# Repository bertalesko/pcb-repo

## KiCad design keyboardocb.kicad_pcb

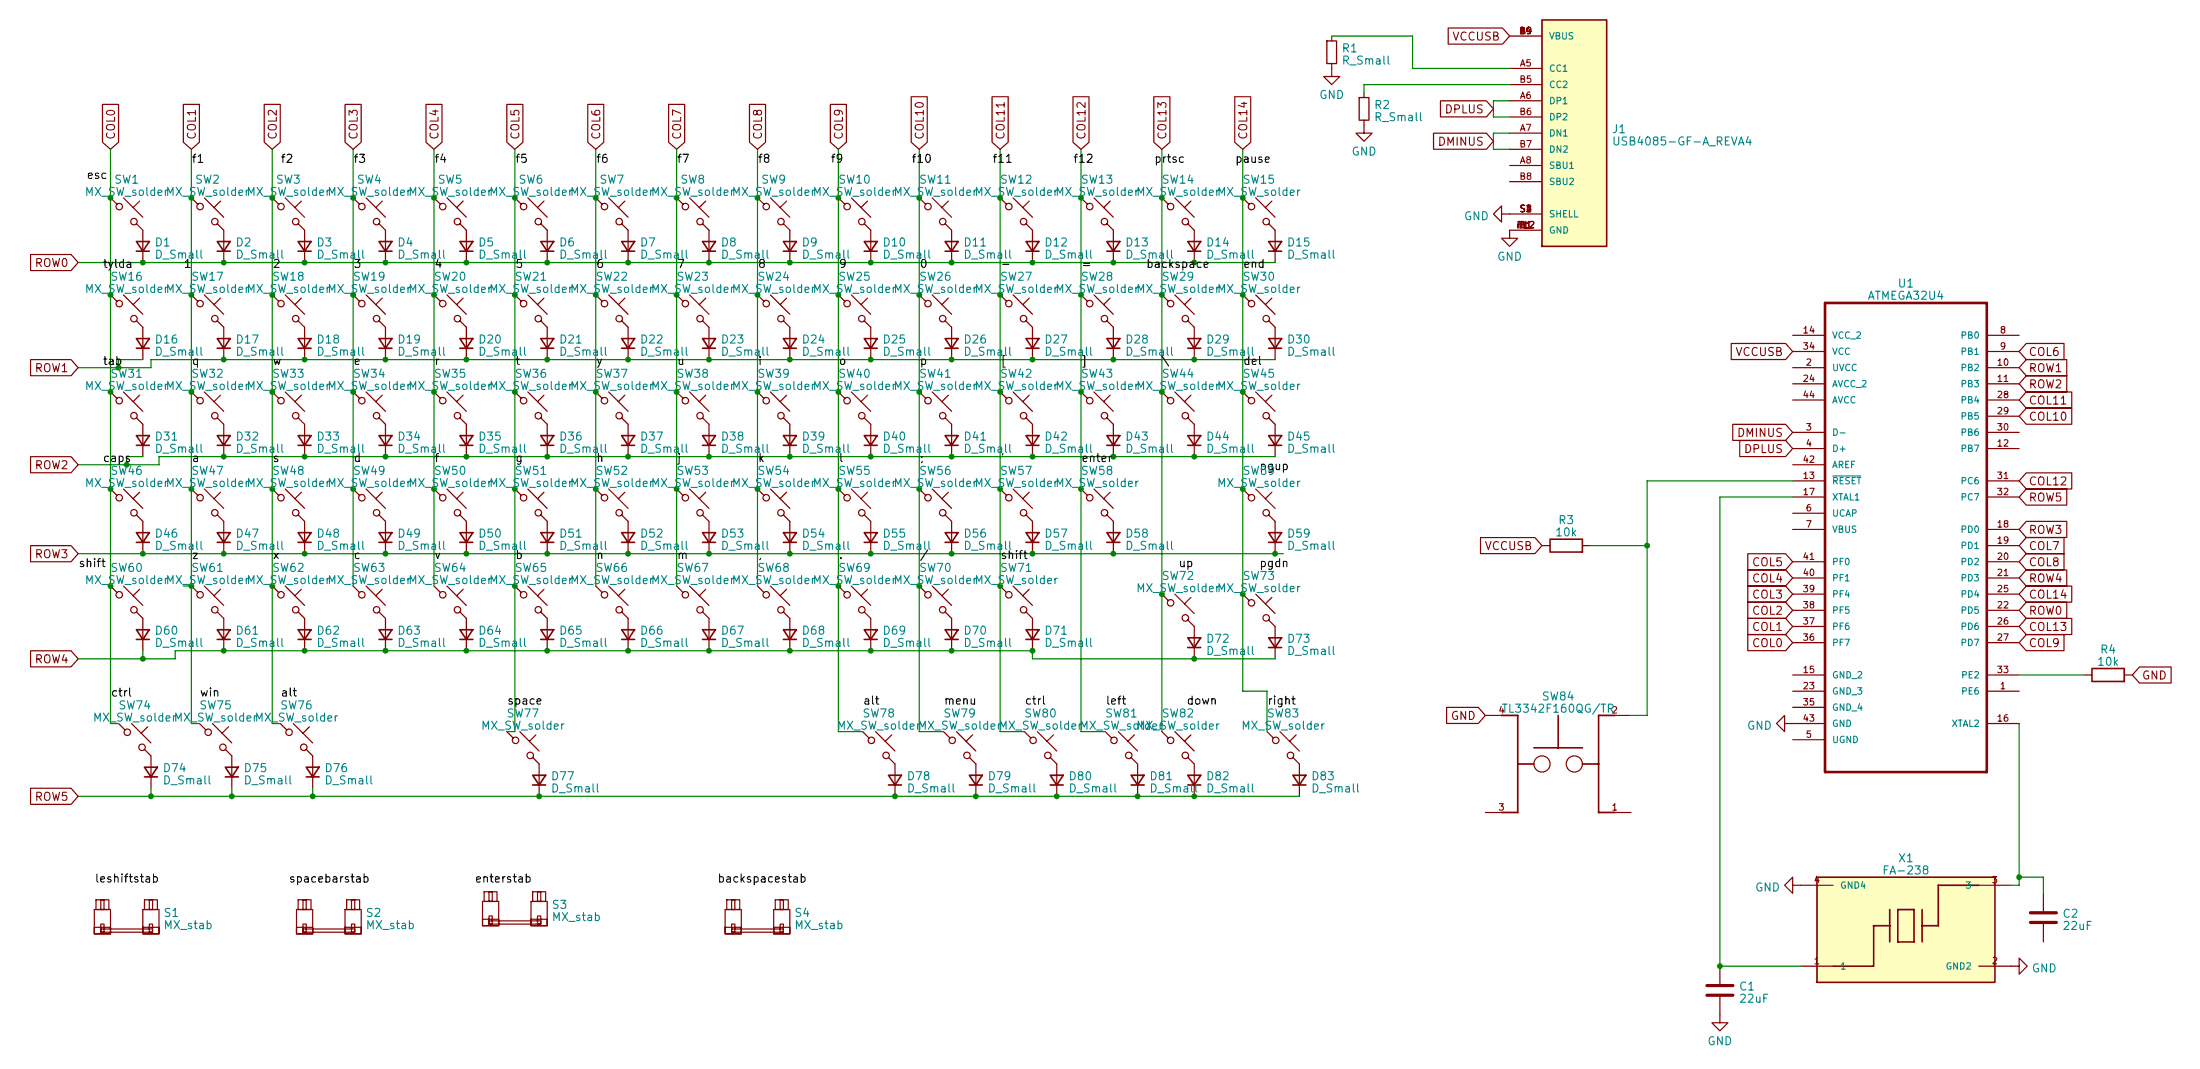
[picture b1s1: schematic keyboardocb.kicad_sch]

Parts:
C1, C2: 22uF; C0805
D1, D2, D3, D4, D5, D6, D7, D8, D9, D10, D11, D12, D13, D14, D15, D16, D17, D18, D19, D20, D21, D22, D23, D24, D25, D26, D27, D28, D29, D30, D31, D32, D33, D34, D35, D36, D37, D38, D39, D40, D41, D42, D43, D44, D45, D46, D47, D48, D49, D50, D51, D52, D53, D54, D55, D56, D57, D58, D59, D60, D61, D62, D63, D64, D65, D66, D67, D68, D69, D70, D71, D72, D73, D74, D75, D76, D77, D78, D79, D80, D81, D82, D83: D_Small; D_SOD-323
J1: USB4085-GF-A_REVA4; GCT_USB4085-GF-A_REVA4; PARTREV A4
R1, R2: R_Small; R0805
R3, R4: 10k; R0805
S1, S3: MX_stab; STAB_MX_P_2.25u
S2: MX_stab; STAB_MX_P_6.25u
S4: MX_stab; STAB_MX_P_2u
SW1, SW2, SW3, SW4, SW5, SW6, SW7, SW8, SW9, SW10, SW11, SW12, SW13, SW14, SW15, SW16, SW17, SW18, SW19, SW20, SW21, SW22, SW23, SW24, SW25, SW26, SW27, SW28, SW29, SW30, SW32, SW33, SW34, SW35, SW36, SW37, SW38, SW39, SW40, SW41, SW42, SW43, SW45, SW47, SW48, SW49, SW50, SW51, SW52, SW53, SW54, SW55, SW56, SW57, SW58, SW59, SW60, SW61, SW62, SW63, SW64, SW65, SW66, SW67, SW68, SW69, SW70, SW72, SW73, SW77, SW78, SW79, SW80, SW81, SW82, SW83: MX_SW_solder; SW_MX_1u
SW31, SW44: MX_SW_solder; SW_MX_1.5u
SW46, SW71: MX_SW_solder; SW_MX_1.75u
SW74, SW75, SW76: MX_SW_solder; SW_MX_1.25u
SW84: TL3342F160QG/TR; SW_TL3342F160QG_TR
U1: ATMEGA32U4; ATmega32U4
X1: FA-238; OSCCC320X250X70-4N

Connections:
COL0: SW1.1, SW16.1, SW31.1, SW46.1, SW60.1, SW74.1, U1.36 (PF7)
COL1: SW2.1, SW17.1, SW32.1, SW47.1, SW61.1, SW75.1, U1.37 (PF6)
COL2: SW3.1, SW18.1, SW33.1, SW48.1, SW62.1, SW76.1, U1.38 (PF5)
COL3: SW4.1, SW19.1, SW34.1, SW49.1, SW63.1, U1.39 (PF4)
COL4: SW5.1, SW20.1, SW35.1, SW50.1, SW64.1, U1.40 (PF1)
COL5: SW6.1, SW21.1, SW36.1, SW51.1, SW65.1, SW77.1, U1.41 (PF0)
COL6: SW7.1, SW22.1, SW37.1, SW52.1, SW66.1, U1.9 (PB1)
COL7: SW8.1, SW23.1, SW38.1, SW53.1, SW67.1, U1.19 (PD1)
COL8: SW9.1, SW24.1, SW39.1, SW54.1, SW68.1, U1.20 (PD2)
COL9: SW10.1, SW25.1, SW40.1, SW55.1, SW69.1, SW78.1, U1.27 (PD7)
COL10: SW11.1, SW26.1, SW41.1, SW56.1, SW70.1, SW79.1, U1.29 (PB5)
COL11: SW12.1, SW27.1, SW42.1, SW57.1, SW71.1, SW80.1, U1.28 (PB4)
COL12: SW13.1, SW28.1, SW43.1, SW58.1, SW81.1, U1.31 (PC6)
COL13: SW14.1, SW29.1, SW44.1, SW72.1, SW82.1, U1.26 (PD6)
COL14: SW15.1, SW30.1, SW45.1, SW59.1, SW73.1, SW83.1, U1.25 (PD4)
DMINUS: J1.A7 (DN1), J1.B7 (DN2), U1.3 (D-)
DPLUS: J1.A6 (DP1), J1.B6 (DP2), U1.4 (D+)
GND: C1.2, J1.A1 (GND), J1.A12 (GND), J1.B1 (GND), J1.B12 (GND), J1.S1 (SHELL), J1.S2 (SHELL), J1.S3 (SHELL), J1.S4 (SHELL), R1.2, R2.2, R4.2, SW84.4, U1.43 (GND), X1.2 (GND2), X1.4 (GND4)
unnamed: D1.2 (A), SW1.2
unnamed: D2.2 (A), SW2.2
unnamed: D3.2 (A), SW3.2
unnamed: D4.2 (A), SW4.2
unnamed: D5.2 (A), SW5.2
unnamed: D6.2 (A), SW6.2
unnamed: D7.2 (A), SW7.2
unnamed: D8.2 (A), SW8.2
unnamed: D9.2 (A), SW9.2
unnamed: D10.2 (A), SW10.2
unnamed: D11.2 (A), SW11.2
unnamed: D12.2 (A), SW12.2
unnamed: D13.2 (A), SW13.2
unnamed: D14.2 (A), SW14.2
unnamed: D15.2 (A), SW15.2
unnamed: D16.2 (A), SW16.2
unnamed: D17.2 (A), SW17.2
unnamed: D18.2 (A), SW18.2
unnamed: D19.2 (A), SW19.2
unnamed: D20.2 (A), SW20.2
unnamed: D21.2 (A), SW21.2
unnamed: D22.2 (A), SW22.2
unnamed: D23.2 (A), SW23.2
unnamed: D24.2 (A), SW24.2
unnamed: D25.2 (A), SW25.2
unnamed: D26.2 (A), SW26.2
unnamed: D27.2 (A), SW27.2
unnamed: D28.2 (A), SW28.2
unnamed: D29.2 (A), SW29.2
unnamed: D30.2 (A), SW30.2
unnamed: D31.2 (A), SW31.2
unnamed: D32.2 (A), SW32.2
unnamed: D33.2 (A), SW33.2
unnamed: D34.2 (A), SW34.2
unnamed: D35.2 (A), SW35.2
unnamed: D36.2 (A), SW36.2
unnamed: D37.2 (A), SW37.2
unnamed: D38.2 (A), SW38.2
unnamed: D39.2 (A), SW39.2
unnamed: D40.2 (A), SW40.2
unnamed: D41.2 (A), SW41.2
unnamed: D42.2 (A), SW42.2
unnamed: D43.2 (A), SW43.2
unnamed: D44.2 (A), SW44.2
unnamed: D45.2 (A), SW45.2
unnamed: D46.2 (A), SW46.2
unnamed: D47.2 (A), SW47.2
unnamed: D48.2 (A), SW48.2
unnamed: D49.2 (A), SW49.2
unnamed: D50.2 (A), SW50.2
unnamed: D51.2 (A), SW51.2
unnamed: D52.2 (A), SW52.2
unnamed: D53.2 (A), SW53.2
unnamed: D54.2 (A), SW54.2
unnamed: D55.2 (A), SW55.2
unnamed: D56.2 (A), SW56.2
unnamed: D57.2 (A), SW57.2
unnamed: D58.2 (A), SW58.2
unnamed: D59.2 (A), SW59.2
unnamed: D60.2 (A), SW60.2
unnamed: D61.2 (A), SW61.2
unnamed: D62.2 (A), SW62.2
unnamed: D63.2 (A), SW63.2
unnamed: D64.2 (A), SW64.2
unnamed: D65.2 (A), SW65.2
unnamed: D66.2 (A), SW66.2
unnamed: D67.2 (A), SW67.2
unnamed: D68.2 (A), SW68.2
unnamed: D69.2 (A), SW69.2
unnamed: D70.2 (A), SW70.2
unnamed: D71.2 (A), SW71.2
unnamed: D72.2 (A), SW72.2
unnamed: D73.2 (A), SW73.2
unnamed: D74.2 (A), SW74.2
unnamed: D75.2 (A), SW75.2
unnamed: D76.2 (A), SW76.2
unnamed: D77.2 (A), SW77.2
unnamed: D78.2 (A), SW78.2
unnamed: D79.2 (A), SW79.2
unnamed: D80.2 (A), SW80.2
unnamed: D81.2 (A), SW81.2
unnamed: D82.2 (A), SW82.2
unnamed: D83.2 (A), SW83.2
unnamed: J1.A5 (CC1), R1.1
unnamed: J1.B5 (CC2), R2.1
unnamed: R4.1, U1.33 (PE2)
unnamed: C1.1, U1.17 (XTAL1), X1.1
unnamed: C2.1, U1.16 (XTAL2), X1.3
unnamed: R3.2, SW84.2, U1.13 (~RESET)
ROW0: D1.1 (K), D2.1 (K), D3.1 (K), D4.1 (K), D5.1 (K), D6.1 (K), D7.1 (K), D8.1 (K), D9.1 (K), D10.1 (K), D11.1 (K), D12.1 (K), D13.1 (K), D14.1 (K), D15.1 (K), U1.22 (PD5)
ROW1: D16.1 (K), D17.1 (K), D18.1 (K), D19.1 (K), D20.1 (K), D21.1 (K), D22.1 (K), D23.1 (K), D24.1 (K), D25.1 (K), D26.1 (K), D27.1 (K), D28.1 (K), D29.1 (K), D30.1 (K), U1.10 (PB2)
ROW2: D31.1 (K), D32.1 (K), D33.1 (K), D34.1 (K), D35.1 (K), D36.1 (K), D37.1 (K), D38.1 (K), D39.1 (K), D40.1 (K), D41.1 (K), D42.1 (K), D43.1 (K), D44.1 (K), D45.1 (K), U1.11 (PB3)
ROW3: D46.1 (K), D47.1 (K), D48.1 (K), D49.1 (K), D50.1 (K), D51.1 (K), D52.1 (K), D53.1 (K), D54.1 (K), D55.1 (K), D56.1 (K), D57.1 (K), D58.1 (K), D59.1 (K), U1.18 (PD0)
ROW4: D60.1 (K), D61.1 (K), D62.1 (K), D63.1 (K), D64.1 (K), D65.1 (K), D66.1 (K), D67.1 (K), D68.1 (K), D69.1 (K), D70.1 (K), D71.1 (K), D72.1 (K), D73.1 (K), U1.21 (PD3)
ROW5: D74.1 (K), D75.1 (K), D76.1 (K), D77.1 (K), D78.1 (K), D79.1 (K), D80.1 (K), D81.1 (K), D82.1 (K), D83.1 (K), U1.32 (PC7)
VCCUSB: J1.A4 (VBUS), J1.A9 (VBUS), J1.B4 (VBUS), J1.B9 (VBUS), R3.1, U1.34 (VCC)

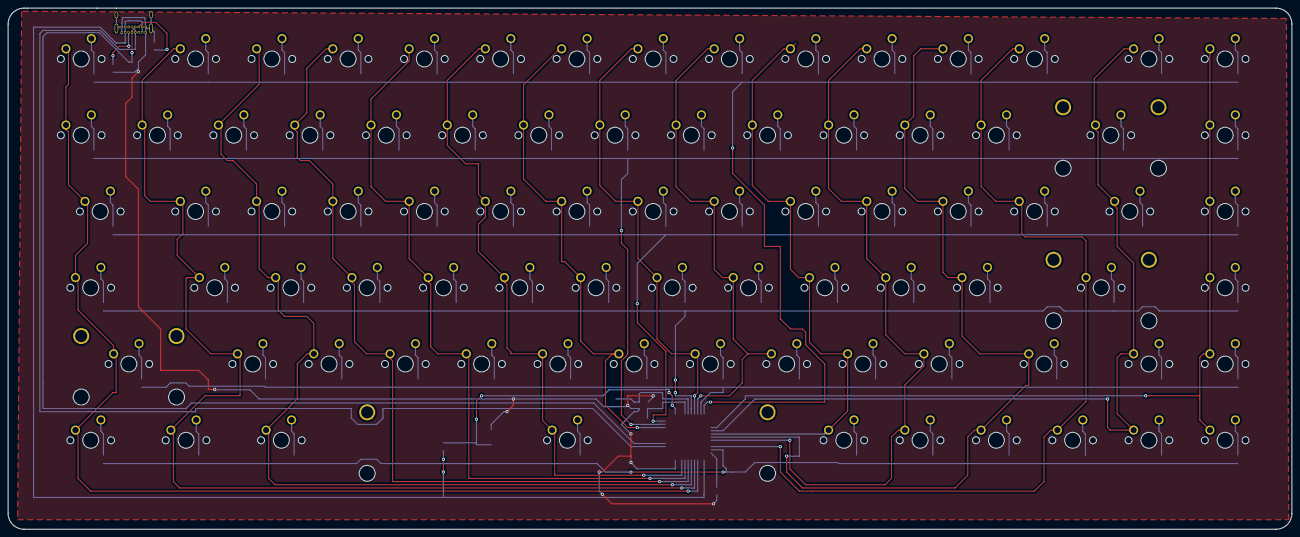
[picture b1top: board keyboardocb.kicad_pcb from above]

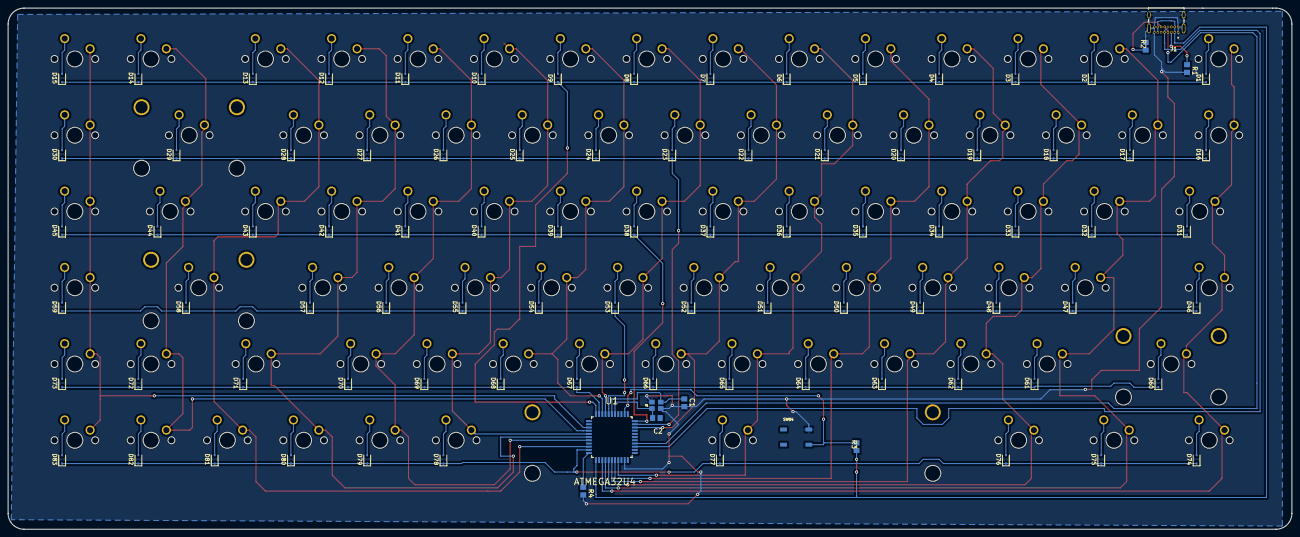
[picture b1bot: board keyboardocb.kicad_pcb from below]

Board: 2 copper layers, 320.7 x 130.2 mm, 180 parts (93 on the bottom side), 114 nets.

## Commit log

2023-03-31 first comm
    1
2023-03-31 Add submodules
2023-03-31 Add submodules2
2023-04-05 updatek
2023-04-05 quickupd
